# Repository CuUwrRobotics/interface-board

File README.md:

# Robot Hardware Interface Board

This repository contains [@nichlock](https://github.com/nichlock)'s design for our hardware interfacing board. This is the board which the [board-interface](https://github.com/CuUwrRobotics/PiranhaBot-docs/blob/master/board_interface/README.md) package is designed to control. 

# Capabilities

This board is designed for our underwater robot, and connects to the Raspebrry Pi through the 40-pin header on the right. It has the following dedicated capabilities:
- 32 GPIO pins
- 32 PWM outputs
- 16 Analog inputs
- 8 Individual leak sensors
- 4 MOSFETs capable of driving 17A (connector limited)
- 2 Current sensors capable of 17A (connector limited, sensors are capable of 50A)
- 1 Microcontroller for I/O that needs constant attention
- 1 Configuration chooser, with 4 switches, for changing any setting on the fly

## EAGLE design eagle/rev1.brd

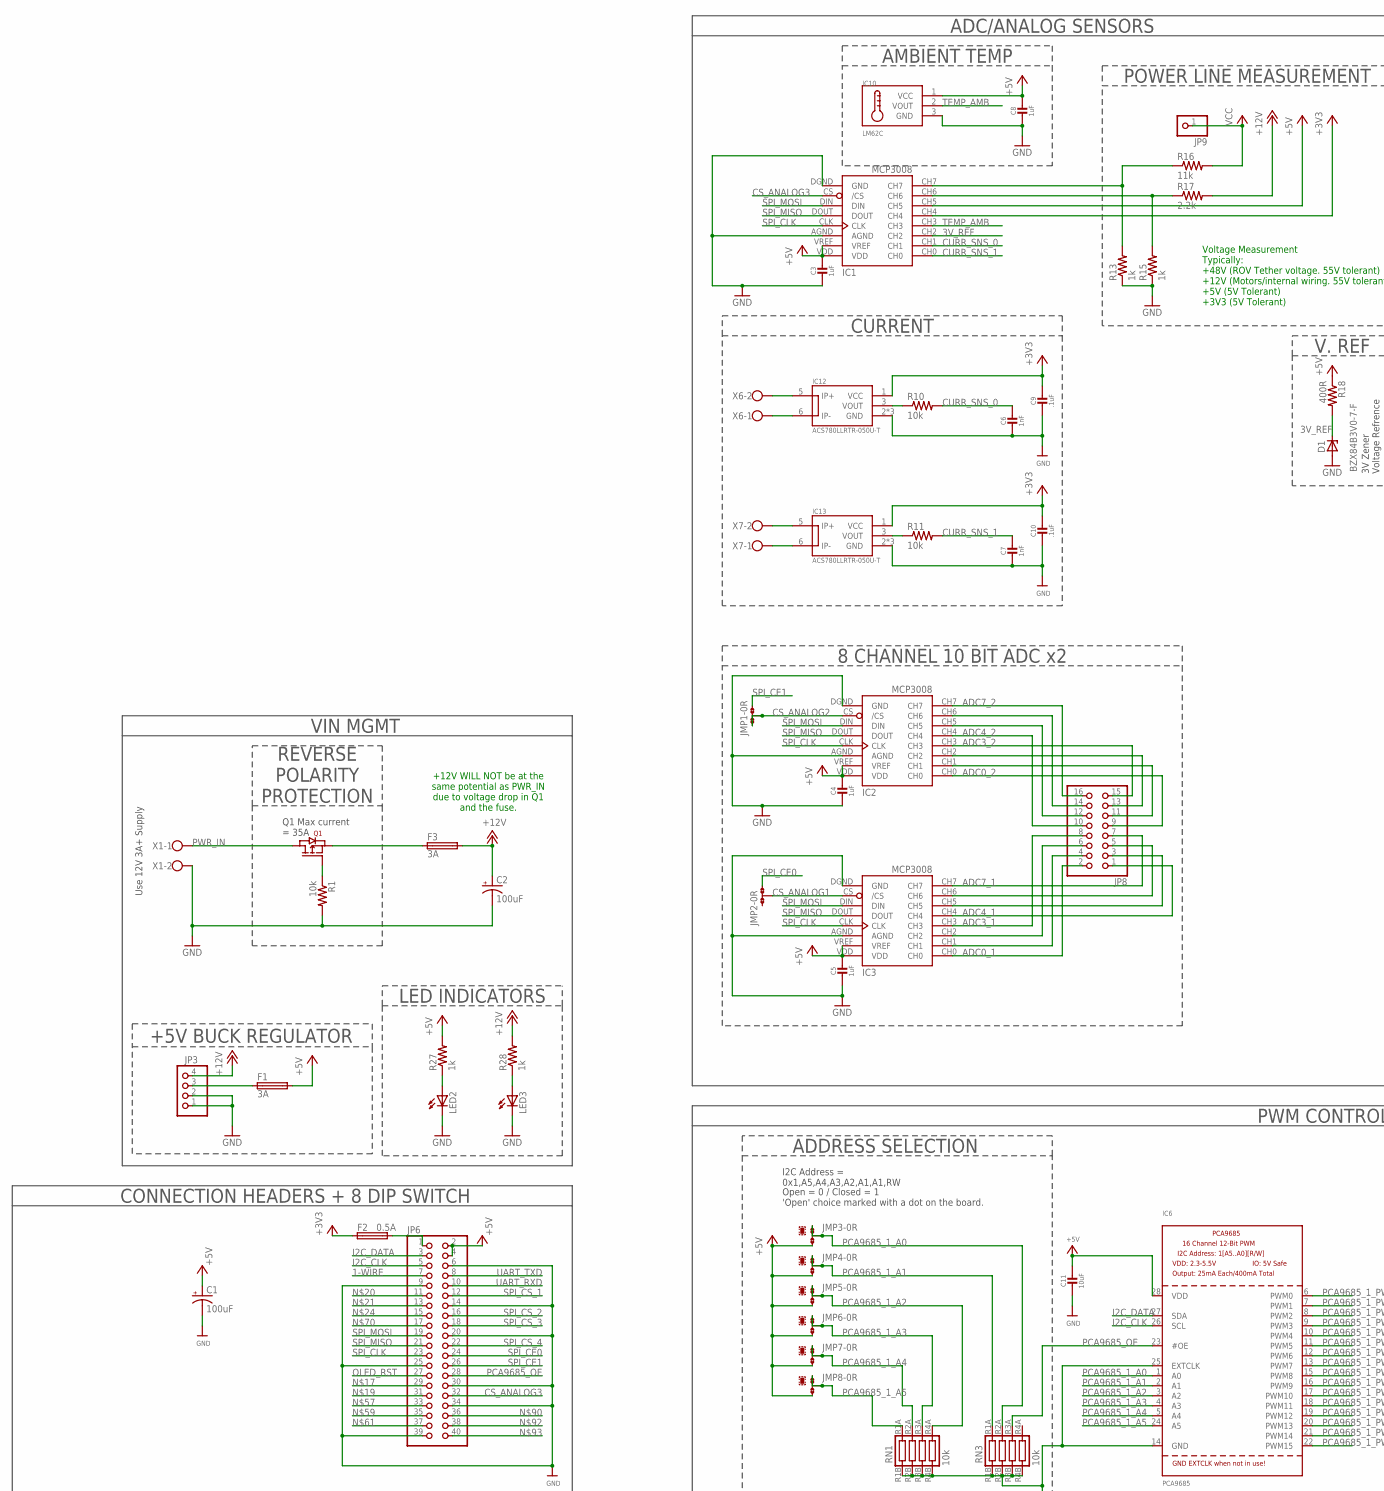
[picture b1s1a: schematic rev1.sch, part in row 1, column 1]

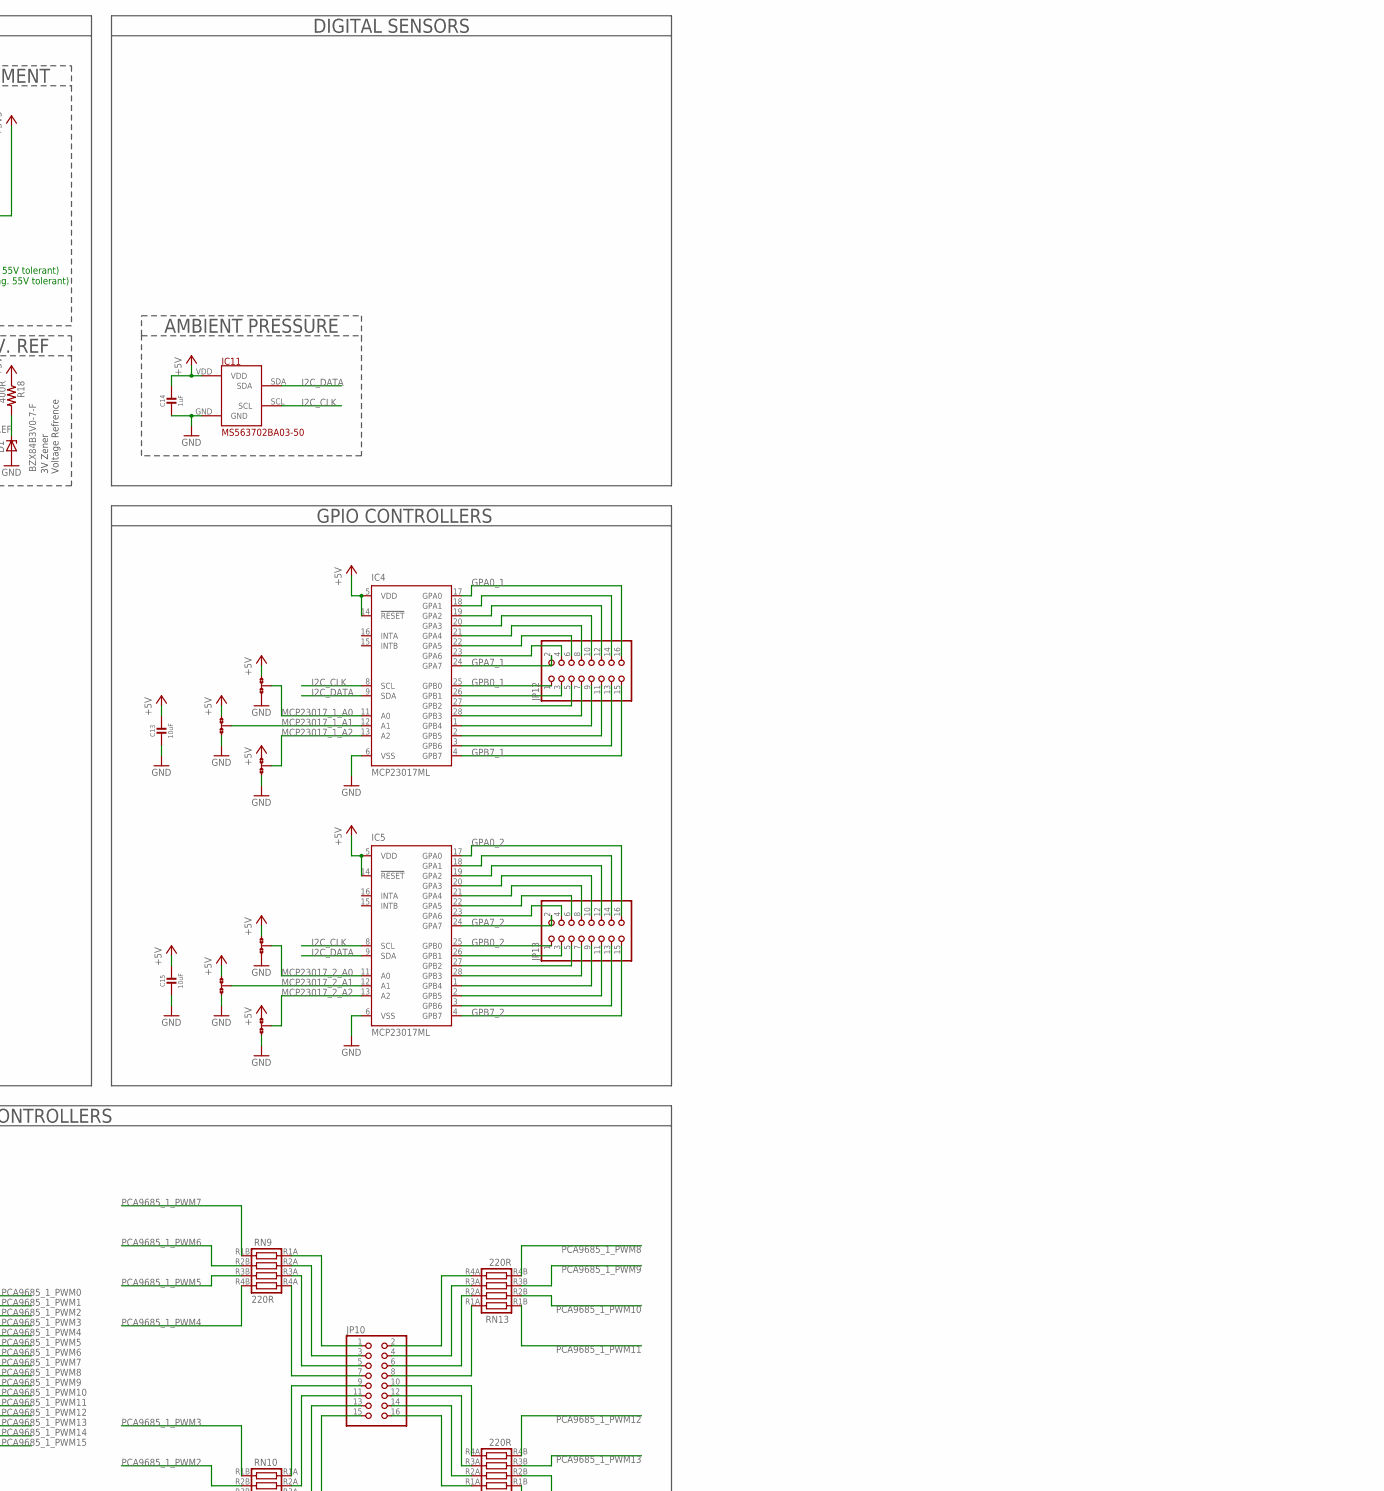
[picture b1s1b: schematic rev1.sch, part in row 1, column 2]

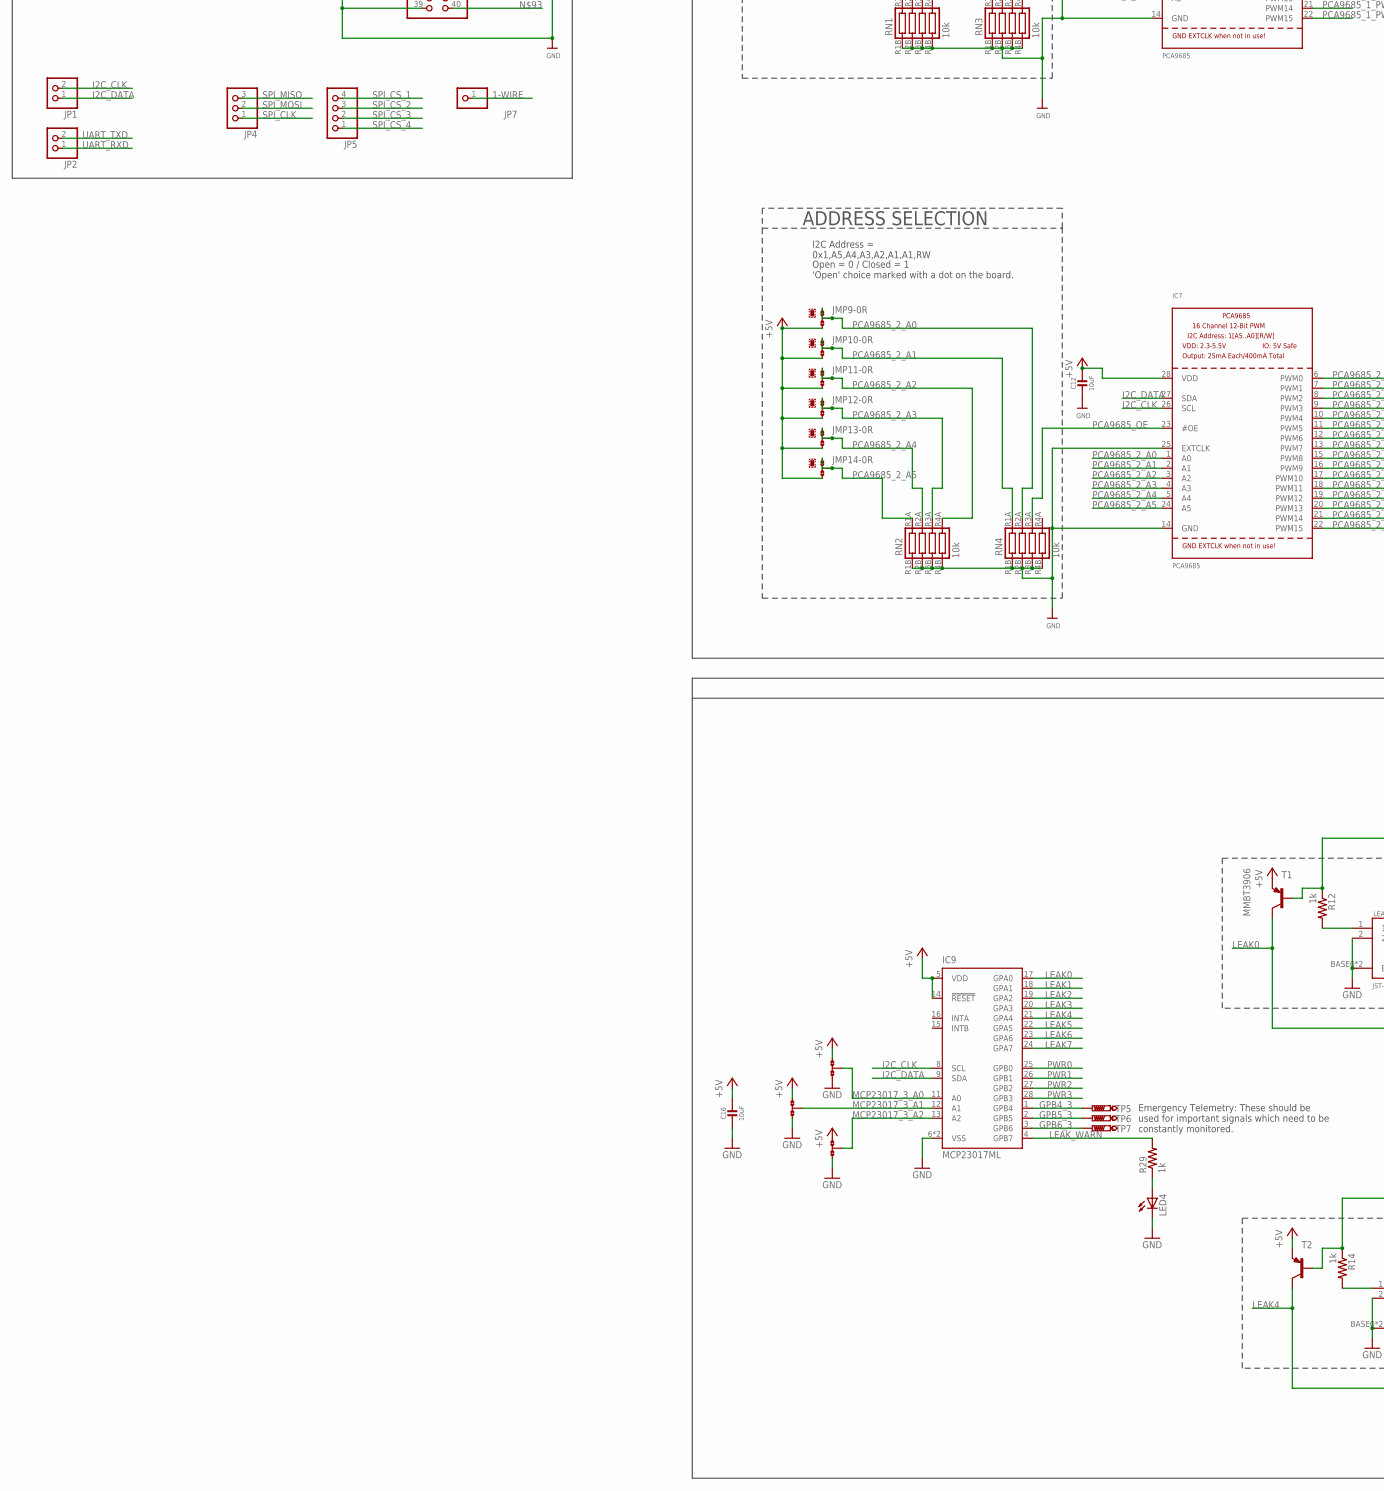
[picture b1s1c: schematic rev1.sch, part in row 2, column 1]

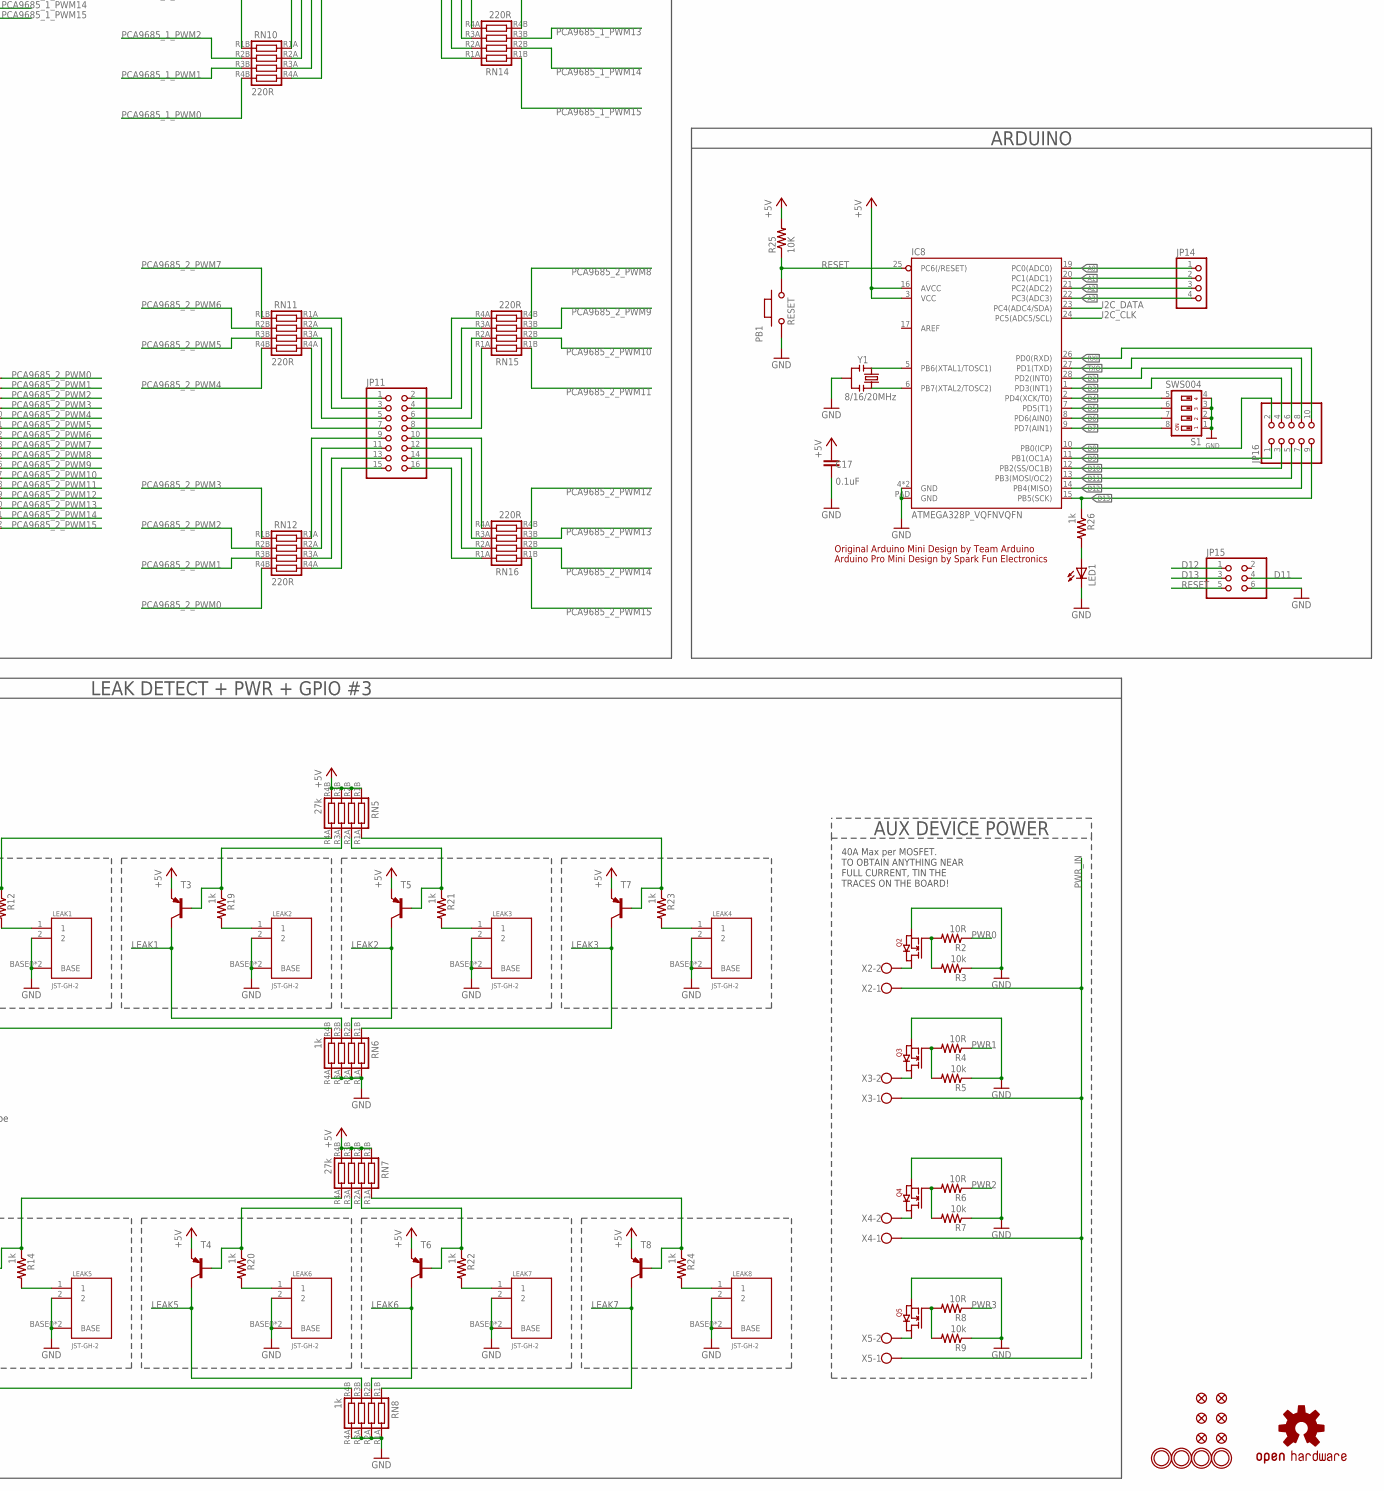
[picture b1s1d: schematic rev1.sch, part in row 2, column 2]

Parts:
1, 2, 3, 4: MOUNTINGHOLE2.5; MOUNTINGHOLE_2.5_PLATED
5: OSHW-LOGOS; OSHW-LOGO-S
C1, C2: 100uF; 153CLV-0807
C3, C4, C5, C8, C14: 1uF; 0805-NO
C6, C7: 1nF; 0805-NO
C9, C10: .1uF; 0805-NO
C11, C12, C13, C15, C16: 10uF; 0805-NO
C17: 0.1uF; C0805
D1: BZX84B3V0-7-F; SOT23
F1, F3: 3A; 2920_(7351_METRIC)
F2: 0.5A; 1210_(3225METRIC)
FID1, FID2, FID3, FID4, FID5, FID6: FIDUCIAL""; FIDUCIAL_1MM
IC1, IC2, IC3: U2; MCP3008
IC4, IC5, IC9: MCP23017ML; QFN28-ML_6X6MM
IC6, IC7: PCA9685; TSSOP28
IC8: ATMEGA328P_VQFNVQFN; VQFN-28
IC10: LM62C; SOT23-R
IC11: MS563702BA03-50; MS5637
IC12, IC13: ACS780LLRTR-050U-T; ACS781
JMP1, JMP2, JMP3, JMP4, JMP5, JMP6, JMP7, JMP8, JMP9, JMP10, JMP11, JMP12, JMP13, JMP14, JMP15, JMP16, JMP17, JMP18, JMP19, JMP20, JMP21, JMP22, JMP23: 0R-JUMPC; C0R-JMP
JP1, JP2: PINHD-1X2; 1X02
JP3, JP5, JP14: PINHD-1X4; 1X04
JP4: PINHD-1X3; 1X03
JP6: PINHD-2X20; 2X20
JP7, JP9: PINHD-1X1; 1X01
JP8, JP10, JP11, JP12, JP13: PINHD-2X8; 2X08
JP15: PINHD-2X3; 2X03
JP16: PINHD-2X5; 2X05
LEAK1, LEAK2, LEAK3, LEAK4, LEAK5, LEAK6, LEAK7, LEAK8: JST-GH-2; JST-GH
LED1, LED2, LED3, LED4: LED_E; LED_1206
PB1: RESET; SMD_157SW
Q1: 1212_PFET; POWERPACK_1212-8
Q2, Q3, Q4, Q5: 1212_NFET; POWERPACK_1212-8
R1, R10, R11: 10k; R0402
R2, R4, R6, R8: 10R; R0805
R3, R5, R7, R9: 10k; R0805
R12, R13, R14, R15, R19, R20, R21, R22, R23, R24: 1k; R0402
R16: 11k; R0402
R17: 2.2k; R0402
R18: 400R; R0402
R25: 10K; R0805
R26, R27, R28, R29: 1k; R0805
RN1, RN2, RN3, RN4: 10k; 0804_RN
RN5, RN7: 27k; 0804_RN
RN6, RN8: 1k; 0804_RN
RN9, RN10, RN11, RN12, RN13, RN14, RN15, RN16: 220R; 0804_RN
S1: SWS004; SMS-004
T1: MMBT3906; SOT23-BEC
T2, T3, T4, T5, T6, T7, T8: BC807-40-PNP-SOT23-BEC; SOT23-BEC
TP5, TP6, TP7: PTR1TP06R; TP06R
X1, X2, X3, X4, X5, X6, X7: W237-102
Y1: 8/16/20MHz; RESONATOR-SMD-1:1

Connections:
1-WIRE: JP6.7, JP7.1
3V_REF: D1.3 (C), IC1.CH2, R18.2
+3V3: C9.1, C10.1, F2.1, IC1.CH4, IC12.1 (VCC), IC13.1 (VCC)
+5V: C1.+, C3.1, C4.1, C5.1, C8.1, C11.1, C12.1, C13.1, C14.1, C15.1, C16.1, C17.2, F1.2, IC1.CH5, IC1.VDD, IC1.VREF, IC2.VDD, IC2.VREF, IC3.VDD, IC3.VREF, IC4.5 (VDD), IC4.14 (!RESET), IC5.5 (VDD), IC5.14 (!RESET), IC6.28 (VDD), IC7.28 (VDD), IC8.3 (VCC), IC8.16 (AVCC), IC9.5 (VDD), IC9.14 (!RESET), IC10.1 (VCC), IC11.VDD, JMP3.3, JMP4.3, JMP5.3, JMP6.3, JMP7.3, JMP8.3, JMP9.3, JMP10.3, JMP11.3, JMP12.3, JMP13.3, JMP14.3, JMP15.1, JMP16.1, JMP17.1, JMP18.1, JMP19.1, JMP20.1, JMP21.1, JMP22.1, JMP23.1, JP6.2, JP6.4, R18.1, R25.2, R27.2, RN5.R1B (1), RN5.R2B (2), RN5.R3B (3), RN5.R4B (4), RN7.R1B (1), RN7.R2B (2), RN7.R3B (3), RN7.R4B (4), T1.E, T2.E, T3.E, T4.E, T5.E, T6.E, T7.E, T8.E
+12V: C2.+, F3.2, JP3.4, R17.2, R28.2
A0: IC8.19 (PC0(ADC0)), JP14.1
A1: IC8.20 (PC1(ADC1)), JP14.2
A2: IC8.21 (PC2(ADC2)), JP14.3
A3: IC8.22 (PC3(ADC3)), JP14.4
ADC0_1: IC3.CH0, JP8.2
ADC0_2: IC2.CH0, JP8.9
ADC3_1: IC3.CH3, JP8.8
ADC3_2: IC2.CH3, JP8.15
ADC4_1: IC3.CH4, JP8.1
ADC4_2: IC2.CH4, JP8.10
ADC7_1: IC3.CH7, JP8.7
ADC7_2: IC2.CH7, JP8.16
CS_ANALOG1: IC3.CS (/CS), JMP2.2
CS_ANALOG2: IC2.CS (/CS), JMP1.2, JMP1.3
CS_ANALOG3: IC1.CS (/CS), JP6.32
CURR_SNS_0: C6.1, IC1.CH1, R10.2
CURR_SNS_1: C7.1, IC1.CH0, R11.2
D2: IC8.28 (PD2(INT0)), JP16.6
D3: IC8.1 (PD3(INT1)), JP16.4
D4: IC8.2 (PD4(XCK/T0)), S1.5
D5: IC8.7 (PD5(T1)), S1.6
D6: IC8.8 (PD6(AIN0)), S1.7
D7: IC8.9 (PD7(AIN1)), S1.8
D8: IC8.10 (PB0(ICP)), JP16.2
D9: IC8.11 (PB1(OC1A)), JP16.1
D10: IC8.12 (PB2(SS/OC1B)), JP16.3
D11: IC8.13 (PB3(MOSI/OC2)), JP15.4, JP16.5
D12: IC8.14 (PB4(MISO)), JP15.1, JP16.7
D13: IC8.15 (PB5(SCK)), JP15.3, JP16.9, R26.1
GND: C1.-, C2.-, C3.2, C4.2, C5.2, C6.2, C7.2, C8.2, C9.2, C10.2, C11.2, C12.2, C13.2, C14.2, C15.2, C16.2, C17.1, D1.1 (A), IC1.AGND, IC1.DGND (GND), IC2.AGND, IC2.DGND (GND), IC3.AGND, IC3.DGND (GND), IC4.6 (VSS), IC5.6 (VSS), IC6.14 (GND), IC6.25 (EXTCLK), IC7.14 (GND), IC7.25 (EXTCLK), IC8.4 (GND), IC8.18 (GND), IC8.PAD (GND), IC9.6 (VSS), IC9.EXP (VSS), IC10.3 (GND), IC11.GND, IC12.2 (GND), IC12.4 (GND), IC12.7 (GND), IC13.2 (GND), IC13.4 (GND), IC13.7 (GND), JMP15.3, JMP16.3, JMP17.3, JMP18.3, JMP19.3, JMP20.3, JMP21.3, JMP22.3, JMP23.3, JP3.1, JP3.2, JP6.6, JP6.9, JP6.14, JP6.20, JP6.25, JP6.30, JP6.34, JP6.39, JP15.6, LEAK1.2, LEAK1.BASE0 (BASE), LEAK1.BASE1 (BASE), LEAK2.2, LEAK2.BASE0 (BASE), LEAK2.BASE1 (BASE), LEAK3.2, LEAK3.BASE0 (BASE), LEAK3.BASE1 (BASE), LEAK4.2, LEAK4.BASE0 (BASE), LEAK4.BASE1 (BASE), LEAK5.2, LEAK5.BASE0 (BASE), LEAK5.BASE1 (BASE), LEAK6.2, LEAK6.BASE0 (BASE), LEAK6.BASE1 (BASE), LEAK7.2, LEAK7.BASE0 (BASE), LEAK7.BASE1 (BASE), LEAK8.2, LEAK8.BASE0 (BASE), LEAK8.BASE1 (BASE), LED1.C, LED2.C, LED3.C, LED4.C, PB1.1, Q2.S1 (SOURCE), Q2.S2 (SOURCE), Q2.S3 (SOURCE), Q3.S1 (SOURCE), Q3.S2 (SOURCE), Q3.S3 (SOURCE), Q4.S1 (SOURCE), Q4.S2 (SOURCE), Q4.S3 (SOURCE), Q5.S1 (SOURCE), Q5.S2 (SOURCE), Q5.S3 (SOURCE), R1.2, R3.1, R5.1, R7.1, R9.1, R13.1, R15.1, RN1.R1B (1), RN1.R2B (2), RN1.R3B (3), RN1.R4B (4), RN2.R1B (1), RN2.R2B (2), RN2.R3B (3), RN2.R4B (4), RN3.R1B (1), RN3.R2B (2), RN3.R3B (3), RN3.R4B (4), RN4.R1B (1), RN4.R2B (2), RN4.R3B (3), RN4.R4B (4), RN6.R1A (1A), RN6.R2A (2A), RN6.R3A (3A), RN6.R4A (4A), RN8.R1A (1A), RN8.R2A (2A), RN8.R3A (3A), RN8.R4A (4A), S1.1, S1.2, S1.3, S1.4, X1.2, Y1.2
GPA0_1: IC4.17 (GPA0), JP12.16
GPA0_2: IC5.17 (GPA0), JP13.16
GPA7_1: IC4.24 (GPA7), JP12.2
GPA7_2: IC5.24 (GPA7), JP13.2
GPB0_1: IC4.25 (GPB0), JP12.1
GPB0_2: IC5.25 (GPB0), JP13.1
GPB4_3: IC9.1 (GPB4), TP5.TP
GPB5_3: IC9.2 (GPB5), TP6.TP
GPB6_3: IC9.3 (GPB6), TP7.TP
GPB7_1: IC4.4 (GPB7), JP12.15
GPB7_2: IC5.4 (GPB7), JP13.15
I2C_CLK: IC4.8 (SCL), IC5.8 (SCL), IC6.26 (SCL), IC7.26 (SCL), IC8.24 (PC5(ADC5/SCL)), IC9.8 (SCL), IC11.SCL, JP1.2, JP6.5
I2C_DATA: IC4.9 (SDA), IC5.9 (SDA), IC6.27 (SDA), IC7.27 (SDA), IC8.23 (PC4(ADC4/SDA)), IC9.9 (SDA), IC11.SDA, JP1.1, JP6.3
LEAK0: IC9.17 (GPA0), RN6.R4B (4), T1.C
LEAK1: IC9.18 (GPA1), RN6.R3B (3), T3.C
LEAK2: IC9.19 (GPA2), RN6.R2B (2), T5.C
LEAK3: IC9.20 (GPA3), RN6.R1B (1), T7.C
LEAK4: IC9.21 (GPA4), RN8.R4B (4), T2.C
LEAK5: IC9.22 (GPA5), RN8.R3B (3), T4.C
LEAK6: IC9.23 (GPA6), RN8.R2B (2), T6.C
LEAK7: IC9.24 (GPA7), RN8.R1B (1), T8.C
LEAK_WARN: IC9.4 (GPB7), R29.2
MCP1_GPA1: IC4.18 (GPA1), JP12.14
MCP1_GPA2: IC4.19 (GPA2), JP12.12
MCP1_GPA7: IC4.23 (GPA6), JP12.4
MCP23017_1_A0: IC4.11 (A0), JMP17.2
MCP23017_1_A1: IC4.12 (A1), JMP15.2
MCP23017_1_A2: IC4.13 (A2), JMP18.2
MCP23017_2_A0: IC5.11 (A0), JMP19.2
MCP23017_2_A1: IC5.12 (A1), JMP16.2
MCP23017_2_A2: IC5.13 (A2), JMP20.2
MCP23017_3_A0: IC9.11 (A0), JMP22.2
MCP23017_3_A1: IC9.12 (A1), JMP21.2
MCP23017_3_A2: IC9.13 (A2), JMP23.2
unnamed: Q2.G (GATE), R2.2, R3.2
unnamed: JP11.14, RN16.R2A (2A)
unnamed: Q1.G (GATE), R1.1
unnamed: LED2.A, R27.1
unnamed: LEAK1.1, R12.2
unnamed: LEAK2.1, R19.2
unnamed: LED3.A, R28.1
unnamed: IC2.CH6, JP8.14
unnamed: LED1.A, R26.2
unnamed: IC2.CH5, JP8.12
unnamed: IC1.CH6, R15.2, R17.1
unnamed: IC8.6 (PB7(XTAL2/TOSC2)), Y1.3
unnamed: R21.1, RN5.R2A (2A), T5.B
unnamed: IC8.5 (PB6(XTAL1/TOSC1)), Y1.1
unnamed: F3.1, Q1.S1 (SOURCE), Q1.S2 (SOURCE), Q1.S3 (SOURCE)
unnamed: LEAK3.1, R21.2
unnamed: LED4.A, R29.1
unnamed: IC3.CH6, JP8.5
unnamed: IC3.CH5, JP8.3
unnamed: JP11.11, RN12.R2A (2A)
unnamed: JP10.7, RN9.R4A (4A)
unnamed: JP10.9, RN10.R1A (1A)
unnamed: JP10.11, RN10.R2A (2A)
unnamed: JP10.13, RN10.R3A (3A)
unnamed: JP10.15, RN10.R4A (4A)
unnamed: JP10.5, RN9.R3A (3A)
unnamed: JP10.3, RN9.R2A (2A)
unnamed: JP10.1, RN9.R1A (1A)
unnamed: JP10.10, RN14.R4A (4A)
unnamed: JP10.12, RN14.R3A (3A)
unnamed: JP10.14, RN14.R2A (2A)
unnamed: JP10.16, RN14.R1A (1A)
unnamed: JP10.8, RN13.R1A (1A)
unnamed: JP10.6, RN13.R2A (2A)
unnamed: JP10.4, RN13.R3A (3A)
unnamed: JP10.2, RN13.R4A (4A)
unnamed: JP11.13, RN12.R3A (3A)
unnamed: JP11.15, RN12.R4A (4A)
unnamed: JP11.7, RN11.R4A (4A)
unnamed: JP11.9, RN12.R1A (1A)
unnamed: JP11.5, RN11.R3A (3A)
unnamed: JP11.3, RN11.R2A (2A)
unnamed: JP11.1, RN11.R1A (1A)
unnamed: JP11.2, RN15.R4A (4A)
unnamed: JP11.4, RN15.R3A (3A)
unnamed: JP11.6, RN15.R2A (2A)
unnamed: JP11.10, RN16.R4A (4A)
unnamed: JP11.8, RN15.R1A (1A)
unnamed: JP11.12, RN16.R3A (3A)
unnamed: Q2.D0 (DRAIN), Q2.D1 (DRAIN), Q2.D2 (DRAIN), Q2.D3 (DRAIN), Q2.D4 (DRAIN), X2.2
unnamed: JP11.16, RN16.R1A (1A)
unnamed: Q3.G (GATE), R4.2, R5.2
unnamed: Q3.D0 (DRAIN), Q3.D1 (DRAIN), Q3.D2 (DRAIN), Q3.D3 (DRAIN), Q3.D4 (DRAIN), X3.2
unnamed: Q4.D0 (DRAIN), Q4.D1 (DRAIN), Q4.D2 (DRAIN), Q4.D3 (DRAIN), Q4.D4 (DRAIN), X4.2
unnamed: Q4.G (GATE), R6.2, R7.2
unnamed: Q5.D0 (DRAIN), Q5.D1 (DRAIN), Q5.D2 (DRAIN), Q5.D3 (DRAIN), Q5.D4 (DRAIN), X5.2
unnamed: IC13.6 (IP-), X7.1
unnamed: F1.1, JP3.3
unnamed: IC3.CH2, JP8.6
unnamed: IC3.CH1, JP8.4
unnamed: F2.2, JP6.1
unnamed: IC2.CH2, JP8.13
unnamed: IC2.CH1, JP8.11
unnamed: R12.1, RN5.R4A (4A), T1.B
unnamed: R14.1, RN7.R4A (4A), T2.B
unnamed: IC5.26 (GPB1), JP13.3
unnamed: IC5.27 (GPB2), JP13.5
unnamed: R19.1, RN5.R3A (3A), T3.B
unnamed: IC5.28 (GPB3), JP13.7
unnamed: IC5.1 (GPB4), JP13.9
unnamed: IC5.2 (GPB5), JP13.11
unnamed: Q5.G (GATE), R8.2, R9.2
unnamed: LEAK4.1, R23.2
unnamed: R23.1, RN5.R1A (1A), T7.B
unnamed: LEAK5.1, R14.2
unnamed: LEAK6.1, R20.2
unnamed: R20.1, RN7.R3A (3A), T4.B
unnamed: IC5.3 (GPB6), JP13.13
unnamed: IC12.5 (IP+), X6.2
unnamed: IC12.6 (IP-), X6.1
unnamed: IC5.23 (GPA6), JP13.4
unnamed: IC5.22 (GPA5), JP13.6
unnamed: IC5.21 (GPA4), JP13.8
unnamed: IC5.20 (GPA3), JP13.10
unnamed: IC5.19 (GPA2), JP13.12
unnamed: IC5.18 (GPA1), JP13.14
unnamed: IC13.5 (IP+), X7.2
unnamed: IC13.3 (VOUT), R11.1
unnamed: IC4.26 (GPB1), JP12.3
unnamed: IC4.27 (GPB2), JP12.5
unnamed: IC4.28 (GPB3), JP12.7
unnamed: IC4.1 (GPB4), JP12.9
unnamed: IC4.2 (GPB5), JP12.11
unnamed: IC4.3 (GPB6), JP12.13
unnamed: LEAK7.1, R22.2
unnamed: IC12.3 (VOUT), R10.1
unnamed: R22.1, RN7.R2A (2A), T6.B
unnamed: IC4.22 (GPA5), JP12.6
unnamed: IC4.21 (GPA4), JP12.8
unnamed: IC4.20 (GPA3), JP12.10
unnamed: LEAK8.1, R24.2
unnamed: R24.1, RN7.R1A (1A), T8.B
OLED_RST: JP6.27
PCA9685_1_A0: IC6.1 (A0), JMP3.1, JMP3.2, RN3.R2A (2A)
PCA9685_1_A1: IC6.2 (A1), JMP4.1, JMP4.2, RN3.R1A (1A)
PCA9685_1_A2: IC6.3 (A2), JMP5.1, JMP5.2, RN1.R4A (4A)
PCA9685_1_A3: IC6.4 (A3), JMP6.1, JMP6.2, RN1.R3A (3A)
PCA9685_1_A4: IC6.5 (A4), JMP7.1, JMP7.2, RN1.R2A (2A)
PCA9685_1_A5: IC6.24 (A5), JMP8.1, JMP8.2, RN1.R1A (1A)
PCA9685_1_PWM0: IC6.6 (PWM0), RN10.R4B (4)
PCA9685_1_PWM1: IC6.7 (PWM1), RN10.R3B (3)
PCA9685_1_PWM2: IC6.8 (PWM2), RN10.R2B (2)
PCA9685_1_PWM3: IC6.9 (PWM3), RN10.R1B (1)
PCA9685_1_PWM4: IC6.10 (PWM4), RN9.R4B (4)
PCA9685_1_PWM5: IC6.11 (PWM5), RN9.R3B (3)
PCA9685_1_PWM6: IC6.12 (PWM6), RN9.R2B (2)
PCA9685_1_PWM7: IC6.13 (PWM7), RN9.R1B (1)
PCA9685_1_PWM8: IC6.15 (PWM8), RN13.R4B (4)
PCA9685_1_PWM9: IC6.16 (PWM9), RN13.R3B (3)
PCA9685_1_PWM10: IC6.17 (PWM10), RN13.R2B (2)
PCA9685_1_PWM11: IC6.18 (PWM11), RN13.R1B (1)
PCA9685_1_PWM12: IC6.19 (PWM12), RN14.R4B (4)
PCA9685_1_PWM13: IC6.20 (PWM13), RN14.R3B (3)
PCA9685_1_PWM14: IC6.21 (PWM14), RN14.R2B (2)
PCA9685_1_PWM15: IC6.22 (PWM15), RN14.R1B (1)
PCA9685_2_A0: IC7.1 (A0), JMP9.1, JMP9.2, RN4.R2A (2A)
PCA9685_2_A1: IC7.2 (A1), JMP10.1, JMP10.2, RN4.R1A (1A)
PCA9685_2_A2: IC7.3 (A2), JMP11.1, JMP11.2, RN2.R4A (4A)
PCA9685_2_A3: IC7.4 (A3), JMP12.1, JMP12.2, RN2.R3A (3A)
PCA9685_2_A4: IC7.5 (A4), JMP13.1, JMP13.2, RN2.R2A (2A)
PCA9685_2_A5: IC7.24 (A5), JMP14.1, JMP14.2, RN2.R1A (1A)
PCA9685_2_PWM0: IC7.6 (PWM0), RN12.R4B (4)
PCA9685_2_PWM1: IC7.7 (PWM1), RN12.R3B (3)
PCA9685_2_PWM2: IC7.8 (PWM2), RN12.R2B (2)
PCA9685_2_PWM3: IC7.9 (PWM3), RN12.R1B (1)
PCA9685_2_PWM4: IC7.10 (PWM4), RN11.R4B (4)
PCA9685_2_PWM5: IC7.11 (PWM5), RN11.R3B (3)
PCA9685_2_PWM6: IC7.12 (PWM6), RN11.R2B (2)
PCA9685_2_PWM7: IC7.13 (PWM7), RN11.R1B (1)
PCA9685_2_PWM8: IC7.15 (PWM8), RN15.R4B (4)
PCA9685_2_PWM9: IC7.16 (PWM9), RN15.R3B (3)
PCA9685_2_PWM10: IC7.17 (PWM10), RN15.R2B (2)
PCA9685_2_PWM11: IC7.18 (PWM11), RN15.R1B (1)
PCA9685_2_PWM12: IC7.19 (PWM12), RN16.R4B (4)
PCA9685_2_PWM13: IC7.20 (PWM13), RN16.R3B (3)
PCA9685_2_PWM14: IC7.21 (PWM14), RN16.R2B (2)
PCA9685_2_PWM15: IC7.22 (PWM15), RN16.R1B (1)
PCA9685_OE: IC6.23 (#OE), IC7.23 (#OE), JP6.28, RN3.R3A (3A), RN4.R3A (3A)
PWR0: IC9.25 (GPB0), R2.1
PWR1: IC9.26 (GPB1), R4.1
PWR2: IC9.27 (GPB2), R6.1
PWR3: IC9.28 (GPB3), R8.1
PWR_IN: Q1.D0 (DRAIN), Q1.D1 (DRAIN), Q1.D2 (DRAIN), Q1.D3 (DRAIN), Q1.D4 (DRAIN), X1.1, X2.1, X3.1, X4.1, X5.1
RESET: IC8.25 (PC6(/RESET)), JP15.5, PB1.2, R25.1
RXI: IC8.26 (PD0(RXD)), JP16.10
SPI_CE0: JMP2.1, JP6.24
SPI_CE1: JMP1.1, JP6.26
SPI_CLK: IC1.CLK, IC2.CLK, IC3.CLK, JP4.1, JP6.23
SPI_CS_1: JP5.4, JP6.12
SPI_CS_2: JP5.3, JP6.16
SPI_CS_3: JP5.2, JP6.18
SPI_CS_4: JP5.1, JP6.22
SPI_MISO: IC1.DOUT, IC2.DOUT, IC3.DOUT, JP4.3, JP6.21
SPI_MOSI: IC1.DIN, IC2.DIN, IC3.DIN, JP4.2, JP6.19
TEMP_AMB: IC1.CH3, IC10.2 (VOUT)
TXO: IC8.27 (PD1(TXD)), JP16.8
UART_RXD: JP2.1, JP6.10
UART_TXD: JP2.2, JP6.8
VBAT_ADC: IC1.CH7, R13.2, R16.1
VCC: JP9.1, R16.2

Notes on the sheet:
+12V WILL NOT be at the same potential as PWR_IN due to voltage drop in Q1 and the fuse.
REVERSE POLARITY PROTECTION
AUX DEVICE POWER
VIN MGMT
LED INDICATORS
Voltage Measurement Typically: +48V (ROV Tether voltage. 55V tolerant) +12V (Motors/internal wiring. 55V tolerant) +5V (5V Tolerant) +3V3 (5V Tolerant)
I2C Address = 0x1,A5,A4,A3,A2,A1,A1,RW
Open = 0 / Closed = 1 'Open' choice marked with a dot on the board.
40A Max per MOSFET. TO OBTAIN ANYTHING NEAR FULL CURRENT, TIN THE TRACES ON THE BOARD!
Q1 Max current = 35A
ADC/ANALOG SENSORS
POWER LINE MEASUREMENT
+5V BUCK REGULATOR
CONNECTION HEADERS + 8 DIP SWITCH
PWM CONTROLLERS
ADDRESS SELECTION
Use 12V 3A+ Supply
GPIO CONTROLLERS
3V Zener Voltage Refrence
DIGITAL SENSORS
AMBIENT PRESSURE
V. REF
AMBIENT TEMP
CURRENT
8 CHANNEL 10 BIT ADC x2
Original Arduino Mini Design by Team Arduino
Arduino Pro Mini Design by Spark Fun Electronics
LEAK DETECT + PWR + GPIO #3
ARDUINO
Emergency Telemetry: These should be used for important signals which need to be constantly monitored.

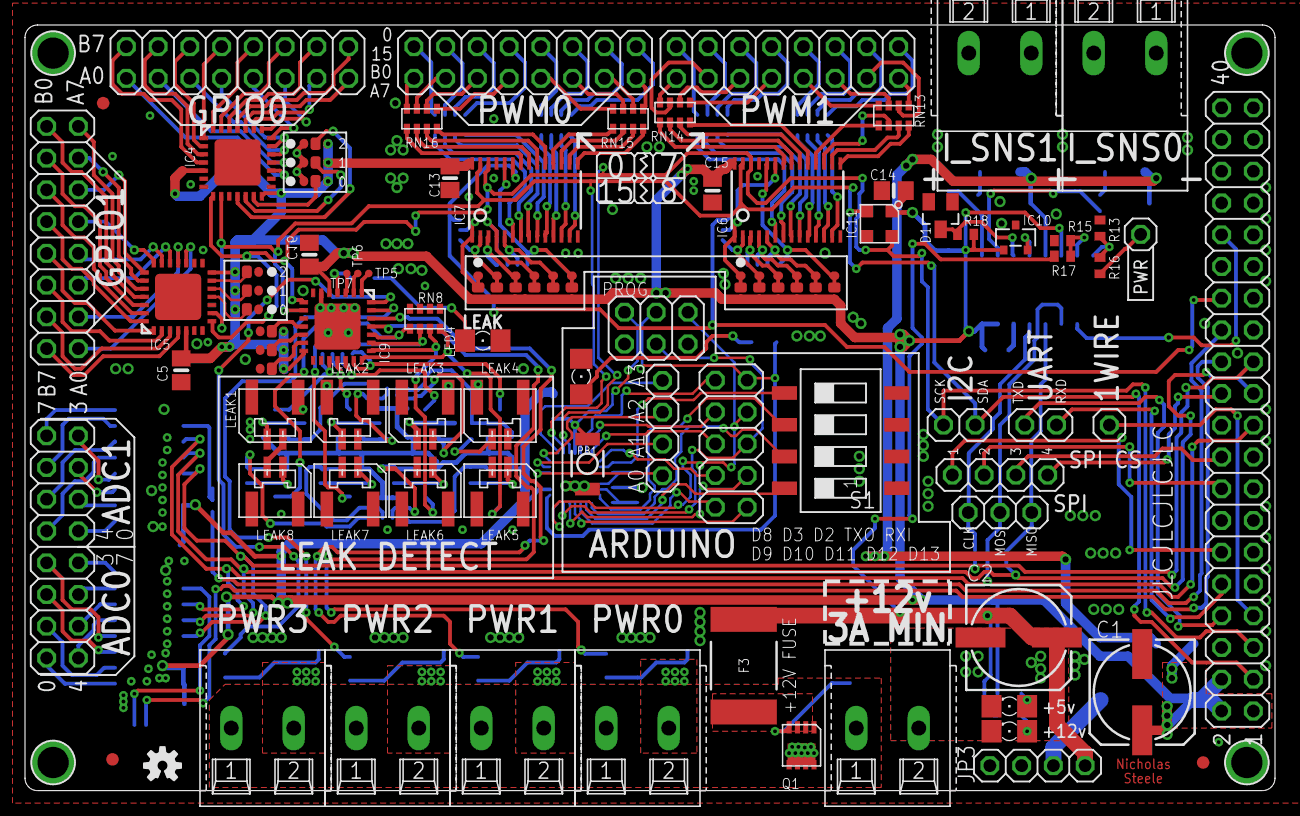
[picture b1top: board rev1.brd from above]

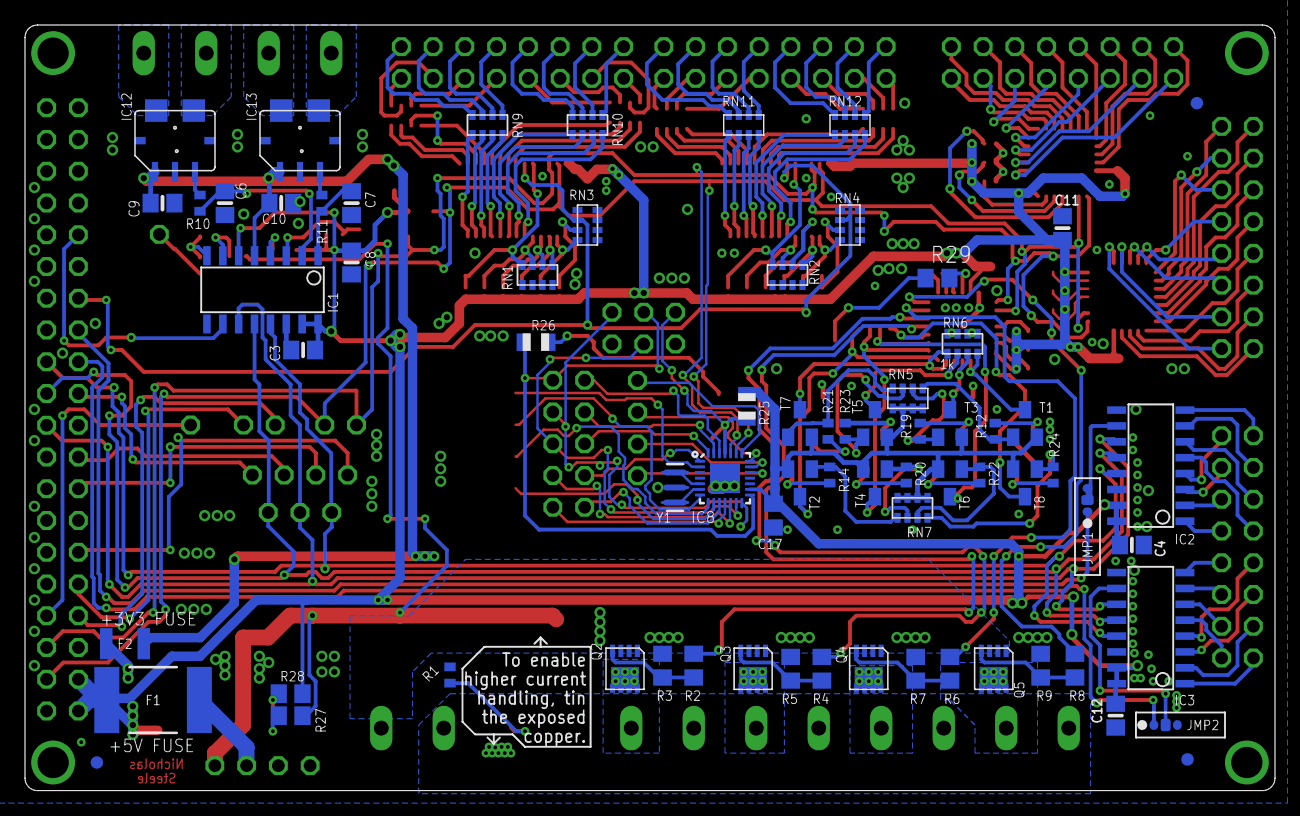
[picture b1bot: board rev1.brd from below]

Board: 2 copper layers, 100.0 x 61.2 mm, 167 parts (71 on the bottom side), 238 nets.

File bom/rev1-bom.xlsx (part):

100 | Value | Device | Package | Description | MFR ID | Mouser P/N | Digikey P/N | Cost | Count | Feature | Include? (1/0) | Cost Impact | Cost impact calc
C1 | 100uF | CPOL-US153CLV-0807 | 153CLV-0807 | Big 5v cap | PCV1J270MCL7GS | 647-PCV1J270MCL7GS |  | 2.82 | x | REQUIRED | x | 10.95 | 71.48
C2 | 100uF | CPOL-US153CLV-0807 | 153CLV-0807 | Big 12v cap | PCV1J270MCL7GS | 647-PCV1J270MCL7GS |  | 2.82 | x | Temp/pressure sensor | x | 3.87 | 31.28000000000004
C3 | 1uF | CAP_CERAMIC0805-NOOUTLINE | 0805-NO | ADC | CC0805ZRY5V7BB105 |  | 311-1457-1-ND | 0.16 | x | Current Sensors | 1 | 13.6 | 40.19999999999996
C4 | 1uF | CAP_CERAMIC0805-NOOUTLINE | 0805-NO | ADC | CC0805ZRY5V7BB105 |  | 311-1457-1-ND | 0.16 | x | Power switching | 1 | 10.08
C5 | 1uF | CAP_CERAMIC0805-NOOUTLINE | 0805-NO | ADC | CC0805ZRY5V7BB105 |  | 311-1457-1-ND | 0.16 | x | Arduino | x | 5.01
C6 | 1nF | CAP_CERAMIC0805-NOOUTLINE | 0805-NO | Current | CC0805JRX7R9BB102 |  | 311-4270-1-ND | 0.16 | 1 | Leak | 1 | 7.6
C7 | 1nF | CAP_CERAMIC0805-NOOUTLINE | 0805-NO | Current | CC0805JRX7R9BB103 |  | 311-4270-1-ND | 0.16 | 1 | ADC | x | 7.05
C8 | 1uF | CAP_CERAMIC0805-NOOUTLINE | 0805-NO | Temp | CC0805ZRY5V7BB105 |  | 311-1457-1-ND | 0.16 | x | GPIO | x | 3.4
C9 | .1uF | CAP_CERAMIC0805-NOOUTLINE | 0805-NO | Current | CC0805ZRY5V9BB104 |  | 311-1361-1-ND | 0.11 | 1 | PWM | x | 6.3
C10 | .1uF | CAP_CERAMIC0805-NOOUTLINE | 0805-NO | Current | CC0805ZRY5V9BB104 |  | 311-1361-1-ND | 0.11 | 1 | Parts for Security cam interface | 0 | 3.52
C11 | 10uF | CAP_CERAMIC0805-NOOUTLINE | 0805-NO | PWM | CC0805ZKY5V7BB106 | 603-CC805ZKY5V7BB106 |  | 0.28999999999999998 | x | Already purchased items marked with x
C12 | 10uF | CAP_CERAMIC0805-NOOUTLINE | 0805-NO | PWM | CC0805ZKY5V7BB106 | 603-CC805ZKY5V7BB106 |  | 0.28999999999999998 | x
C13 | 10uF | CAP_CERAMIC0805-NOOUTLINE | 0805-NO | GPIO | CC0805ZKY5V7BB106 | 603-CC805ZKY5V7BB106 |  | 0.28999999999999998 | x
C14 | 1uF | CAP_CERAMIC0805-NOOUTLINE | 0805-NO | PRESS | CC0805ZRY5V7BB105 |  | 311-1457-1-ND | 0.16 | x
C15 | 10uF | CAP_CERAMIC0805-NOOUTLINE | 0805-NO | GPIO | CC0805ZKY5V7BB106 | 603-CC805ZKY5V7BB106 |  | 0.28999999999999998 | x
C16 | 10uF | CAP_CERAMIC0805-NOOUTLINE | 0805-NO | Leak | CC0805ZKY5V7BB106 | 603-CC805ZKY5V7BB106 |  | 0.28999999999999998 | 1
C17 | 0.1uF | C-EUC0805 | C0805 | Arduino | CC0805ZRY5V9BB104 |  | 311-1361-1-ND | 0.11 | x
D1 | BZX84B3V0-7-F | ZENER-DIODESOT23 | SOT23 | vref | BZX84B3V0-7-F | 621-BZX84B3V0-7-F |  | 0.17 | x
F1 | 3A | PTC_FUSE3 | 2920_(7351_METRIC) | 5v fuse | MF-LSMF300/24X-2 | 652-MF-LSMF300/24X-2 |  | 0.73 | x
F2 | 0.5A | PTC_FUSE2 | 1210_(3225METRIC) | 3v3 fuse | 0ZCH0050FF2G | 530-0ZCH0050FF2G |  | 0.11 | x
F3 | 3A | PTC_FUSE3 | 2920_(7351_METRIC) | 12v fuse | MF-LSMF300/24X-2 | 652-MF-LSMF300/24X-2 |  | 0.73 | x
IC1 | U2 | MCP3008 | MCP3008 | ADC | MCP3008-I/SL |  | MCP3008-I/SL-ND | 2.19 | x
IC2 | U2 | MCP3008 | MCP3008 | ADC | MCP3008-I/SL |  | MCP3008-I/SL-ND | 2.19 | x
IC3 | U2 | MCP3008 | MCP3008 | ADC | MCP3008-I/SL |  | MCP3008-I/SL-ND | 2.19 | x
IC4 | MCP23017ML | MCP23017ML | QFN28-ML_6X6MM | GPIO | MCP23017T-E/ML |  | MCP23017T-E/MLCT-ND | 1.41 | x
IC5 | MCP23017ML | MCP23017ML | QFN28-ML_6X6MM | GPIO | MCP23017T-E/ML |  | MCP23017T-E/MLCT-ND | 1.41 | x
IC6 | PCA9685 | PCA9685 | TSSOP28 | PWM | PCA9685PW/Q900,118 | 771-PCA9685PW,118 |  | 2.2599999999999998 | x
IC7 | PCA9685 | PCA9685 | TSSOP28 | PWM | PCA9685PW/Q900,118 | 771-PCA9685PW,118 |  | 2.2599999999999998 | x
IC8 | ATMEGA328P_VQFNVQFN | ATMEGA328P_VQFNVQFN | VQFN-28 | Arduino | ATMEGA328P-MMHR |  | ATMEGA328P-MMHRCT-ND | 2.17 | x
IC9 | MCP23017ML | MCP23017ML | QFN28-ML_6X6MM | Leak | MCP23017T-E/ML |  | MCP23017T-E/MLCT-ND | 1.41 | 1
IC10 | LM62C | LM62C | SOT23-R | Temp | LM62CIM3/NOPB |  | LM62CIM3/NOPBCT-ND | 1.1299999999999999 | x
IC11 | MS563702BA03-50 | PRESSURE | MS5637 | PRESS | MS563702BA03-50 | 824-MS563702BA03-50 |  | 2.42 | x
IC12 | ACS780LLRTR-050B-T | ACS781 | ACS781 | Current, 100A | ACS780LLRTR-100U-T |  | 620-1820-1-ND | 5.27 | 1
IC13 | ACS780LLRTR-050B-T | ACS781 | ACS781 | Current, 50A | ACS780LLRTR-050U-T |  | 620-1818-1-ND | 5.27 | 1
LEAK1 | JST-GH-2 | JST-GH-2 | JST-GH | Leak | BM02B-GHS-TBT(LF)(SN)(N) |  | 455-1578-1-ND | 0.43 | 1
LEAK2 | JST-GH-2 | JST-GH-2 | JST-GH | Leak | BM02B-GHS-TBT(LF)(SN)(N) |  | 455-1578-1-ND | 0.43 | 1
LEAK3 | JST-GH-2 | JST-GH-2 | JST-GH | Leak | BM02B-GHS-TBT(LF)(SN)(N) |  | 455-1578-1-ND | 0.43 | 1
LEAK4 | JST-GH-2 | JST-GH-2 | JST-GH | Leak | BM02B-GHS-TBT(LF)(SN)(N) |  | 455-1578-1-ND | 0.43 | 1
LEAK5 | JST-GH-2 | JST-GH-2 | JST-GH | Leak | BM02B-GHS-TBT(LF)(SN)(N) |  | 455-1578-1-ND | 0.43 | 1
LEAK6 | JST-GH-2 | JST-GH-2 | JST-GH | Leak | BM02B-GHS-TBT(LF)(SN)(N) |  | 455-1578-1-ND | 0.43 | 1
LEAK7 | JST-GH-2 | JST-GH-2 | JST-GH | Leak | BM02B-GHS-TBT(LF)(SN)(N) |  | 455-1578-1-ND | 0.43 | 1
LEAK8 | JST-GH-2 | JST-GH-2 | JST-GH | Leak | BM02B-GHS-TBT(LF)(SN)(N) |  | 455-1578-1-ND | 0.43 | 1
LED1 |  | LED_E | LED_1206 | Arduino | LTST-C230KFKT | 859-LTST-C230KFKT |  | 0.3 | x
LED2 |  | LED_E | LED_1206 | 5v led | LTST-C230KFKT | 859-LTST-C230KFKT |  | 0.3 | x
LED3 |  | LED_E | LED_1206 | 12v led | LTST-C230KFKT | 859-LTST-C230KFKT |  | 0.3 | x
LED4 |  | LED_E | LED_1206 | Leak | LTST-C230KFKT | 859-LTST-C230KFKT |  | 0.3 | 1
PB1 | RESET | 0173_IT-1185AP1C-160G-G_T&R | SMD_157SW | Arduino | PTS820 J20M SMTR LFS |  | CKN10505CT-ND | 0.45 | x
Q1 | 1212_PFET | 1212_PFET | POWERPACK_1212-8 | reverse polarity | SI7625DN-T1-GE3 | 781-SI7625DN-T1-GE3 |  | 1.01 | x
Q2 | 1212_NFET | 1212_NFET | POWERPACK_1212-8 | pwr | SIS476DN-T1-GE3 |  | SIS476DN-T1-GE3CT-ND | 1.1599999999999999 | 1
Q3 | 1212_NFET | 1212_NFET | POWERPACK_1212-8 | pwr | SIS476DN-T1-GE3 |  | SIS476DN-T1-GE3CT-ND | 1.1599999999999999 | 1
Q4 | 1212_NFET | 1212_NFET | POWERPACK_1212-8 | pwr | SIS476DN-T1-GE3 |  | SIS476DN-T1-GE3CT-ND | 1.1599999999999999 | 1
Q5 | 1212_NFET | 1212_NFET | POWERPACK_1212-8 | pwr | SIS476DN-T1-GE3 |  | SIS476DN-T1-GE3CT-ND | 1.1599999999999999 | 1
R1 | 10k | R-US_R0402 | R0402 | reverse polarity | RC0805FR-0710KL |  | 311-10.0KCRCT-ND | 0.1 | x
R2 | 10R | R-US_R0805 | R0805 | pwr |  |  |  | 0.1 | 1
R3 | 10k | R-US_R0805 | R0805 | pwr | RC0805FR-0710KL |  | 311-10.0KCRCT-ND | 0.1 | 1
R4 | 10R | R-US_R0805 | R0805 | pwr |  |  |  | 0.1 | 1
R5 | 10k | R-US_R0805 | R0805 | pwr | RC0805FR-0710KL |  | 311-10.0KCRCT-ND | 0.1 | 1
R6 | 10R | R-US_R0805 | R0805 | pwr |  |  |  | 0.1 | 1
R7 | 10k | R-US_R0805 | R0805 | pwr | RC0805FR-0710KL |  | 311-10.0KCRCT-ND | 0.1 | 1
R8 | 10R | R-US_R0805 | R0805 | pwr |  |  |  | 0.1 | 1
R9 | 10k | R-US_R0805 | R0805 | pwr | RC0805FR-0710KL |  | 311-10.0KCRCT-ND | 0.1 | 1
R10 | 10k | R-US_R0402 | R0402 | Current | RC0805FR-0710KL |  | 311-10.0KCRCT-ND | 0.1 | 1
R11 | 10k | R-US_R0402 | R0402 | Current | RC0805FR-0710KL |  | 311-10.0KCRCT-ND | 0.1 | 1
R12 | 1k | R-US_R0402 | R0402 | Leak | RC0402FR-071KL |  | 311-1.00KLRCT-ND | 0.1 | 1
R13 | 1k | R-US_R0402 | R0402 | power line measure | RC0402FR-071KL |  | 311-1.00KLRCT-ND | 0.1 | x
R14 | 1k | R-US_R0402 | R0402 | Leak | RC0402FR-071KL |  | 311-1.00KLRCT-ND | 0.1 | 1
R15 | 1k | R-US_R0402 | R0402 | power line measure | RC0402FR-071KL |  | 311-1.00KLRCT-ND | 0.1 | x
R16 | 11k | R-US_R0402 | R0402 | power line measure | RC0402FR-0711KL |  | 311-11.0KLRCT-ND | 0.1 | x
R17 | 2.2k | R-US_R0402 | R0402 | power line measure | RC0402FR-072K2L |  | 311-2.20KLRCT-ND | 0.1 | x
R18 | 1k | R-US_R0402 | R0402 | vref | RC0402FR-071KL |  | 311-1.00KLRCT-ND | 0.1 | x
R19 | 1k | R-US_R0402 | R0402 | Leak | RC0402FR-071KL |  | 311-1.00KLRCT-ND | 0.1 | 1
R20 | 1k | R-US_R0402 | R0402 | Leak | RC0402FR-071KL |  | 311-1.00KLRCT-ND | 0.1 | 1
R21 | 1k | R-US_R0402 | R0402 | Leak | RC0402FR-071KL |  | 311-1.00KLRCT-ND | 0.1 | 1
R22 | 1k | R-US_R0402 | R0402 | Leak | RC0402FR-071KL |  | 311-1.00KLRCT-ND | 0.1 | 1
R23 | 1k | R-US_R0402 | R0402 | Leak | RC0402FR-071KL |  | 311-1.00KLRCT-ND | 0.1 | 1
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

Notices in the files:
parts and their libraries:
SparkFun-IC-Microcontroller: Licensing: Creative Commons ShareAlike 4.0 International - https://creativecommons.org/licenses/by-sa/4.0
